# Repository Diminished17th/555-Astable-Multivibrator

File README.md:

# 12V 555 Timer Astable Multivibrator (1Hz)

This project features a simple 555 timer-based astable multivibrator circuit operating at approximately **1Hz** using a **12V DC supply**.  
It was designed in **KiCad** and simulated using **LTspice**.

---

## 📂 Project Files
| File Name                | Description                      |
|--------------------------|----------------------------------|
| `555_Timer.asc`          | LTspice simulation schematic     |
| `555_timer.kicad_sch`    | KiCad schematic design           |
| `555_timer.kicad_pcb`    | KiCad PCB layout                 |

---

## ⚡ Key Features
- **Operating Voltage:** 12V DC
- **Frequency Output:** ~1Hz square wave
- **Core Component:** NE555 Timer IC
- **Stable astable multivibrator operation**
- Suitable for basic timing, blinking LEDs, or low-frequency pulsing.

---

## 🛠️ Tools Used
- **LTspice**: for circuit simulation and waveform analysis
- **KiCad**: for schematic capture and PCB design

---

## 🧠 Design Notes
- The resistor and capacitor values were selected to achieve a 1-second ON and OFF cycle.
- Special attention was given to maintaining frequency stability over supply voltage variations.
- PCB designed for easy assembly and testing.

---

## 📷 Screenshots

### Schematic

### PCB Layout

### 3D View

### 3D View (Back Side)

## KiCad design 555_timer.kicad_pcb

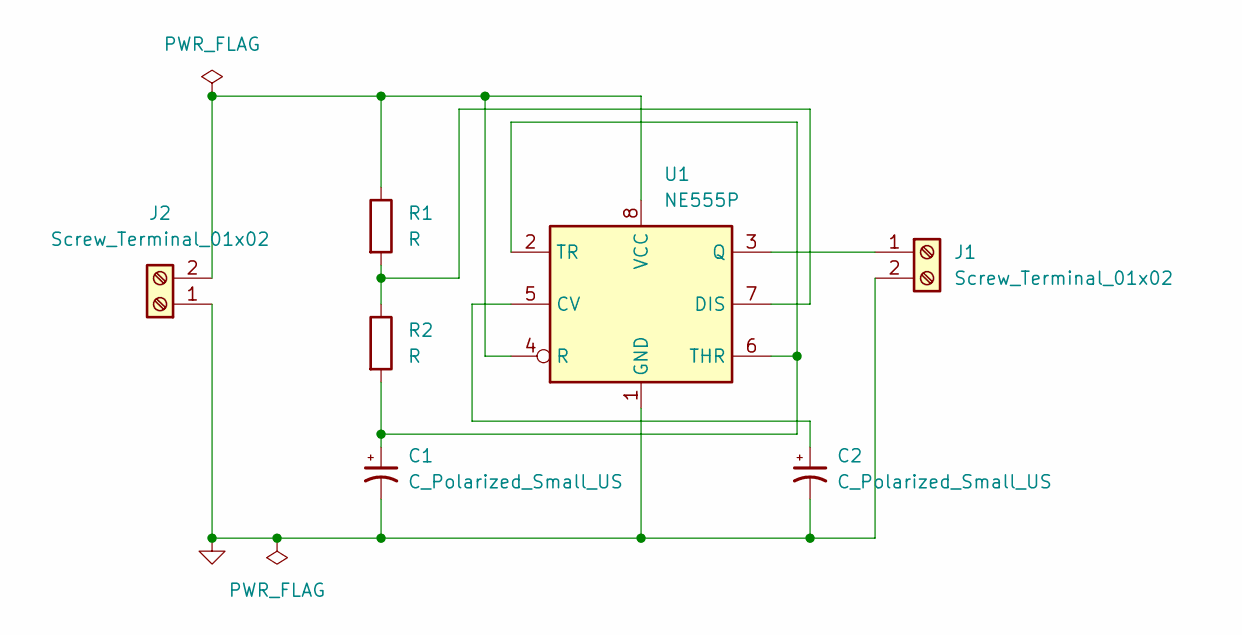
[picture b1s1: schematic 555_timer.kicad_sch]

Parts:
C1, C2: C_Polarized_Small_US; CP_Radial_D5.0mm_P2.00mm
J1, J2: Screw_Terminal_01x02; TerminalBlock_4Ucon_1x02_P3.50mm_Horizontal
R1, R2: R; R_Axial_DIN0207_L6.3mm_D2.5mm_P7.62mm_Horizontal
U1: NE555P; DIP-8_W7.62mm

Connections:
GND: C1.2, C2.2, J1.2, J2.1, U1.1 (GND)
unnamed: J1.1, U1.3 (Q)
unnamed: J2.2, R1.1, U1.4 (R), U1.8 (VCC)
unnamed: C2.1, U1.5 (CV)
unnamed: R1.2, R2.1, U1.7 (DIS)
unnamed: C1.1, R2.2, U1.2 (TR), U1.6 (THR)

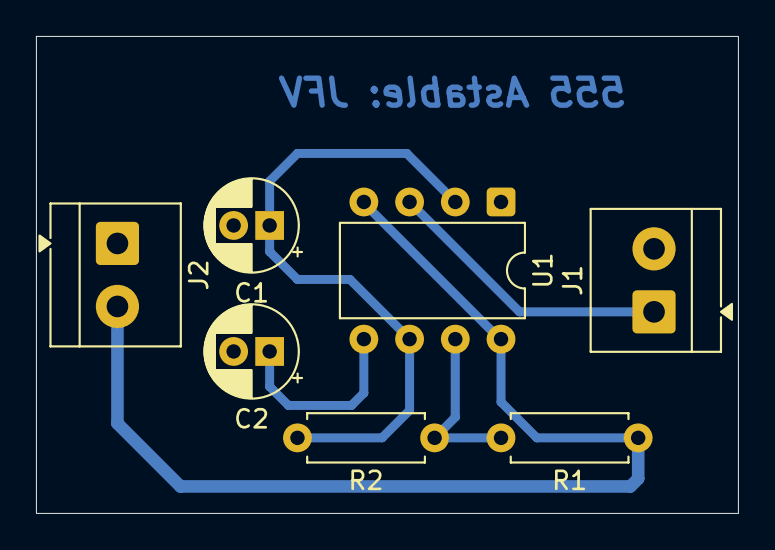
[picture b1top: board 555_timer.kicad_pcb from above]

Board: 2 copper layers, 39.0 x 26.5 mm, 7 parts (0 on the bottom side), 6 nets.

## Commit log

2025-04-26 Uploaded LTspice and KiCad files
2025-04-26 Add images
